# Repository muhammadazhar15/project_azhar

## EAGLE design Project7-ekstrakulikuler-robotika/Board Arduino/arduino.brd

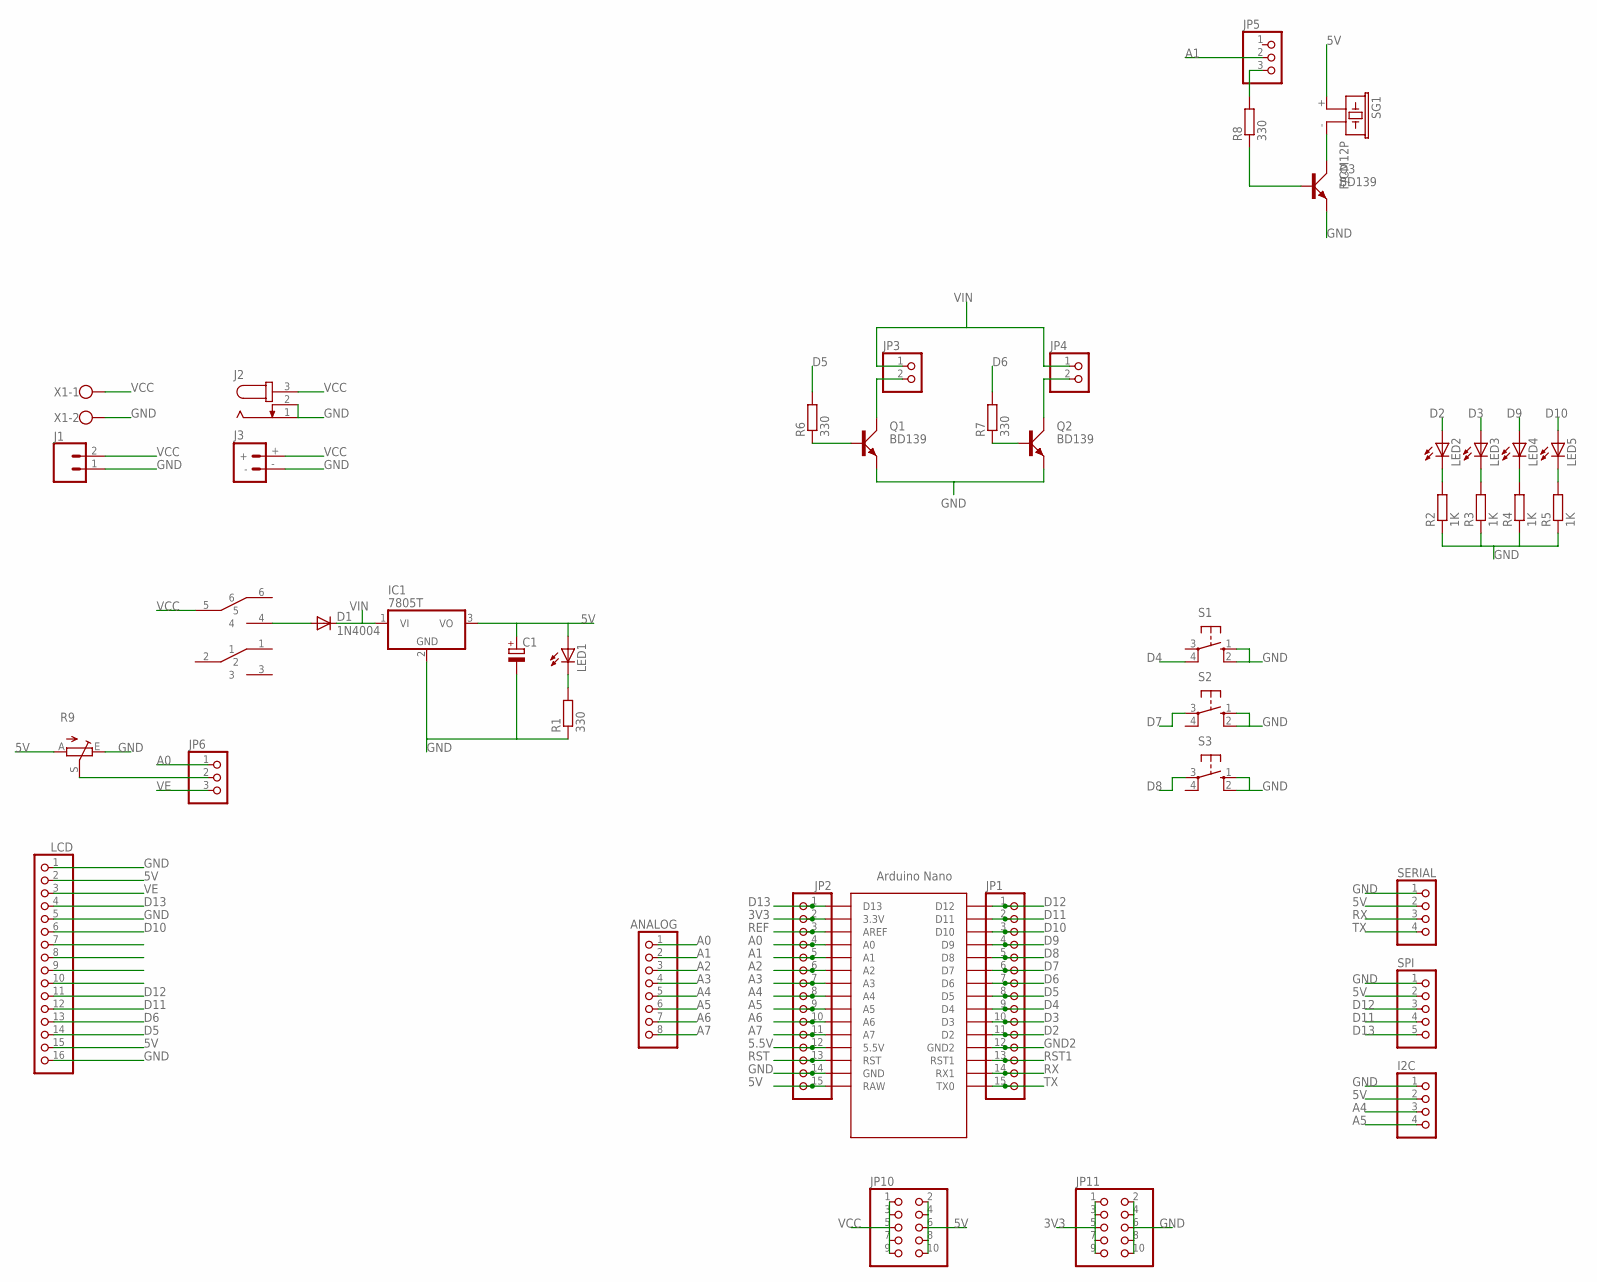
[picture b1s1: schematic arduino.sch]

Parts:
ANALOG: PINHD-1X8; 1X08
C1: CPOL-EUE5-8.5; E5-8,5
D1: 1N4004; DO41-10
I2C: PINHD-1X4; 1X04
IC1: 7805T; TO220H
J1: CONN_02POLAR_LOCK; MOLEX-1X2_LOCK
J2: JACK-PLUG0; SPC4077
J3: BATTERY_CONN_DEANS; DEANS
JP1, JP2: PINHD-1X15; 1X15
JP3, JP4: PINHD-1X2; 1X02
JP5, JP6: PINHD-1X3; 1X03
JP10, JP11: PINHD-2X5; 2X05
LCD: PINHD-1X16; 1X16
LED1, LED2, LED3, LED4, LED5: LED3MM
Q1, Q2, Q3: BD139; TO126AV
R1, R6, R7, R8: 330; 0207/7
R2, R3, R4, R5: 1K; 0207/7
R9: TRIM_EU-CA6V; CA6V
S1, S2, S3: 10-XX; B3F-10XX
SERIAL: PINHD-1X4; 1X04
SG1: F/CM12P
SPI: PINHD-1X5; 1X05
U$1: NANO
U$2: BUTTON-DPDT-7MM
X1: W237-102

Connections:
3V3: JP2.2, JP11.1, JP11.3, JP11.5, JP11.7, JP11.9, U$1.3.3V
5.5V: JP2.12, U$1.5V (5.5V)
5V: C1.+, I2C.2, IC1.3 (VO), JP2.15, JP10.2, JP10.4, JP10.6, JP10.8, JP10.10, LCD.2, LCD.15, LED1.A, R9.A, SERIAL.2, SG1.+ (1), SPI.2, U$1.RAW
A0: ANALOG.1, JP2.4, JP6.1, U$1.A0
A1: ANALOG.2, JP2.5, JP5.2, U$1.A1
A2: ANALOG.3, JP2.6, U$1.A2
A3: ANALOG.4, JP2.7, U$1.A3
A4: ANALOG.5, I2C.3, JP2.8, U$1.A4
A5: ANALOG.6, I2C.4, JP2.9, U$1.A5
A6: ANALOG.7, JP2.10, U$1.A6
A7: ANALOG.8, JP2.11, U$1.A7
D2: JP1.11, LED2.A, U$1.D2
D3: JP1.10, LED3.A, U$1.D3
D4: JP1.9, S1.4 (P1), U$1.D4
D5: JP1.8, LCD.14, R6.2, U$1.D5
D6: JP1.7, LCD.13, R7.2, U$1.D6
D7: JP1.6, S2.3, U$1.D7
D8: JP1.5, S3.3, U$1.D8
D9: JP1.4, LED4.A, U$1.D9
D10: JP1.3, LCD.6, LED5.A, U$1.D10
D11: JP1.2, LCD.12, SPI.4, U$1.D11
D12: JP1.1, LCD.11, SPI.3, U$1.D12
D13: JP2.1, LCD.4, SPI.5, U$1.D13
GND: C1.-, I2C.1, IC1.2 (GND), J1.1, J2.1, J2.2, J3.-, JP2.14, JP11.2, JP11.4, JP11.6, JP11.8, JP11.10, LCD.1, LCD.5, LCD.16, Q1.E, Q2.E, Q3.E, R1.1, R2.1, R3.1, R4.1, R5.1, R9.E, S1.1 (S), S1.2 (S1), S2.1 (S), S2.2 (S1), S3.1 (S), S3.2 (S1), SERIAL.1, SPI.1, U$1.GND, X1.2
GND2: JP1.12, U$1.GND1 (GND2)
unnamed: D1.A, U$2.4
unnamed: Q3.B, R8.1
unnamed: LED2.K (C), R2.2
unnamed: LED1.K (C), R1.2
unnamed: LED3.K (C), R3.2
unnamed: LED4.K (C), R4.2
unnamed: LED5.K (C), R5.2
unnamed: Q1.B, R6.1
unnamed: Q2.B, R7.1
unnamed: JP3.2, Q1.C
unnamed: JP4.2, Q2.C
unnamed: Q3.C, SG1.- (2)
unnamed: JP5.3, R8.2
unnamed: JP6.2, R9.S
REF: JP2.3, U$1.AREF
RST: JP2.13, U$1.RST
RST1: JP1.13, U$1.RST1
RX: JP1.14, SERIAL.3, U$1.RX1
TX: JP1.15, SERIAL.4, U$1.TX0
VCC: J1.2, J2.3, J3.+, JP10.1, JP10.3, JP10.5, JP10.7, JP10.9, U$2.5, X1.1
VE: JP6.3, LCD.3
VIN: D1.C, IC1.1 (VI), JP3.1, JP4.1

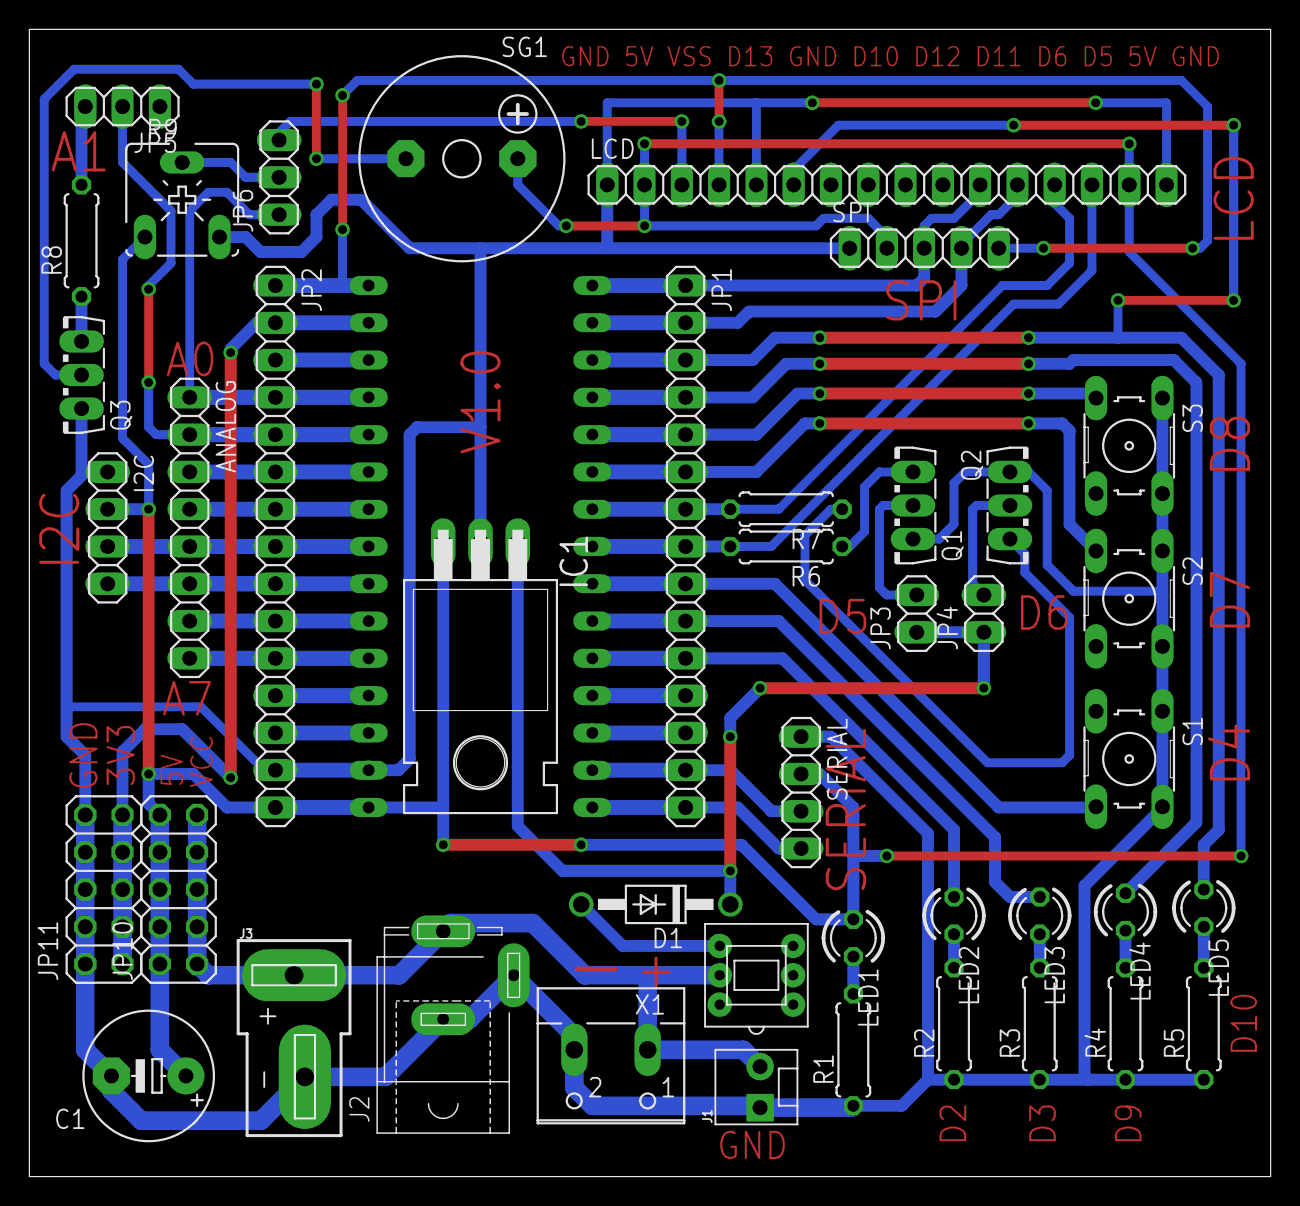
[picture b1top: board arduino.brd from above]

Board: 2 copper layers, 84.6 x 78.2 mm, 43 parts (0 on the bottom side), 47 nets.

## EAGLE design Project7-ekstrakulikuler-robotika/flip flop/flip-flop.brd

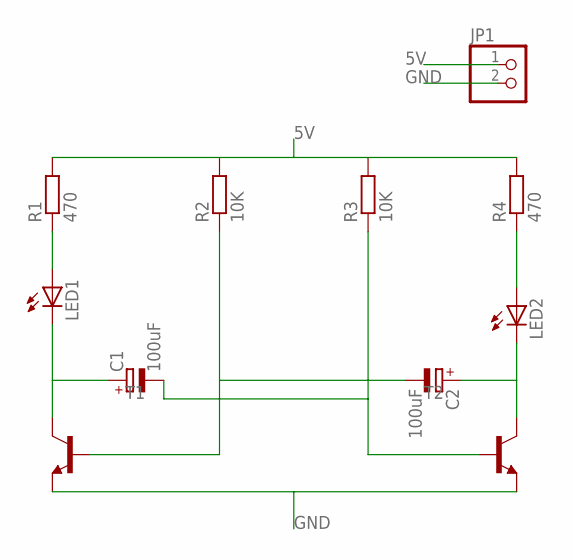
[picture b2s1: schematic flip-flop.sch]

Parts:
C1, C2: 100uF; E2,5-6
JP1: PINHD-1X2; 1X02
LED1, LED2: LED3MM
R1, R4: 470; 0207/7
R2, R3: 10K; 0207/7
T1, T2: BC547-NPN-TO92-CBE; TO92-CBE

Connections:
5V: JP1.1, R1.2, R2.2, R3.2, R4.2
GND: JP1.2, T1.E, T2.E
unnamed: LED1.A, R1.1
unnamed: LED2.A, R4.1
unnamed: C1.+, LED1.K (C), T1.C
unnamed: C2.+, LED2.K (C), T2.C
unnamed: C2.-, R2.1, T1.B
unnamed: C1.-, R3.1, T2.B

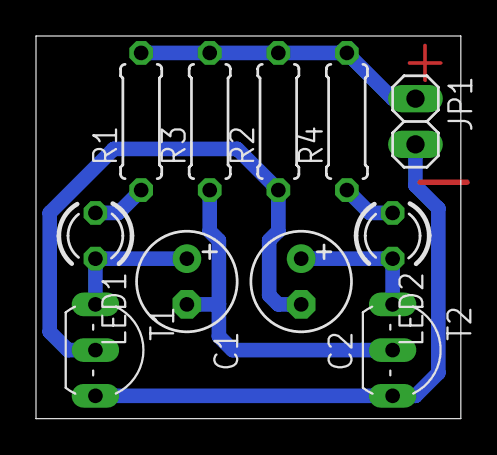
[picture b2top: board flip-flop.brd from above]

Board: 2 copper layers, 23.6 x 21.3 mm, 11 parts (0 on the bottom side), 8 nets.

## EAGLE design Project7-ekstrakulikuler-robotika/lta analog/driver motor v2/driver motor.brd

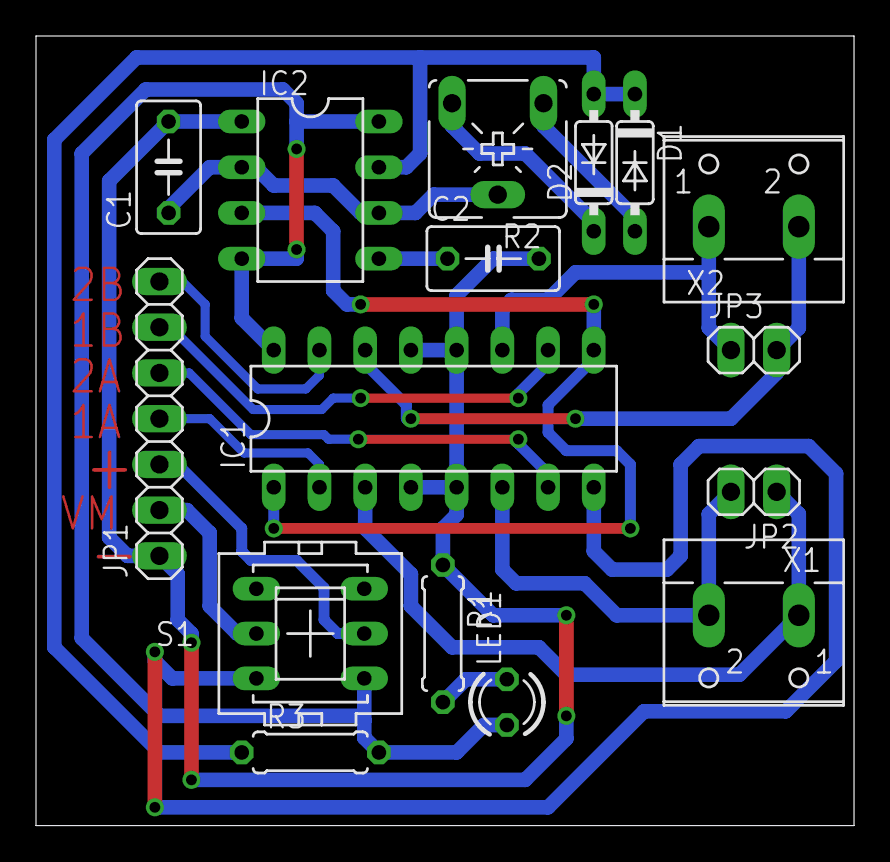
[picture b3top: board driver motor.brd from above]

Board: 2 copper layers, 45.4 x 43.9 mm, 16 parts (0 on the bottom side), 20 nets.

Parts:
C1, C2: C050-035X075
D1, D2: DO35-7
IC1: L293D; DIL16
IC2: NE555; DIL-08
JP1: 1X07
JP2, JP3: 1X02
LED1: LED3MM
R1: 330; 0207/7
R2: 10K; CA6V
R3: 1K; 0207/7
S1: PVA2R
X1, X2: W237-102

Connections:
1A: IC1.2, JP1.4
1B: IC1.10, JP1.6
2A: IC1.7, JP1.5
2B: IC1.15, JP1.7
5V: JP1.3, S1.2
GND: C1.2, C2.2, IC1.4, IC1.5, IC1.12, IC1.13, IC2.1, JP1.1, R1.1
unnamed: LED1.K, R1.2
unnamed: C2.1, IC2.5
unnamed: D1.C, D2.A, IC2.7, R3.1
unnamed: D1.A, R2.A
unnamed: D2.C, R2.E
unnamed: C1.1, IC2.2, IC2.6, R2.S
O1A: IC1.3, JP2.1, X1.1
O1B: IC1.11, JP3.1, X2.1
O2A: IC1.6, JP2.2, X1.2
O2B: IC1.14, JP3.2, X2.2
O5V: IC1.16, IC2.4, IC2.8, LED1.A, R3.2, S1.1
OVIN: IC1.8, S1.4
PWM: IC1.1, IC1.9, IC2.3
VIN: JP1.2, S1.5

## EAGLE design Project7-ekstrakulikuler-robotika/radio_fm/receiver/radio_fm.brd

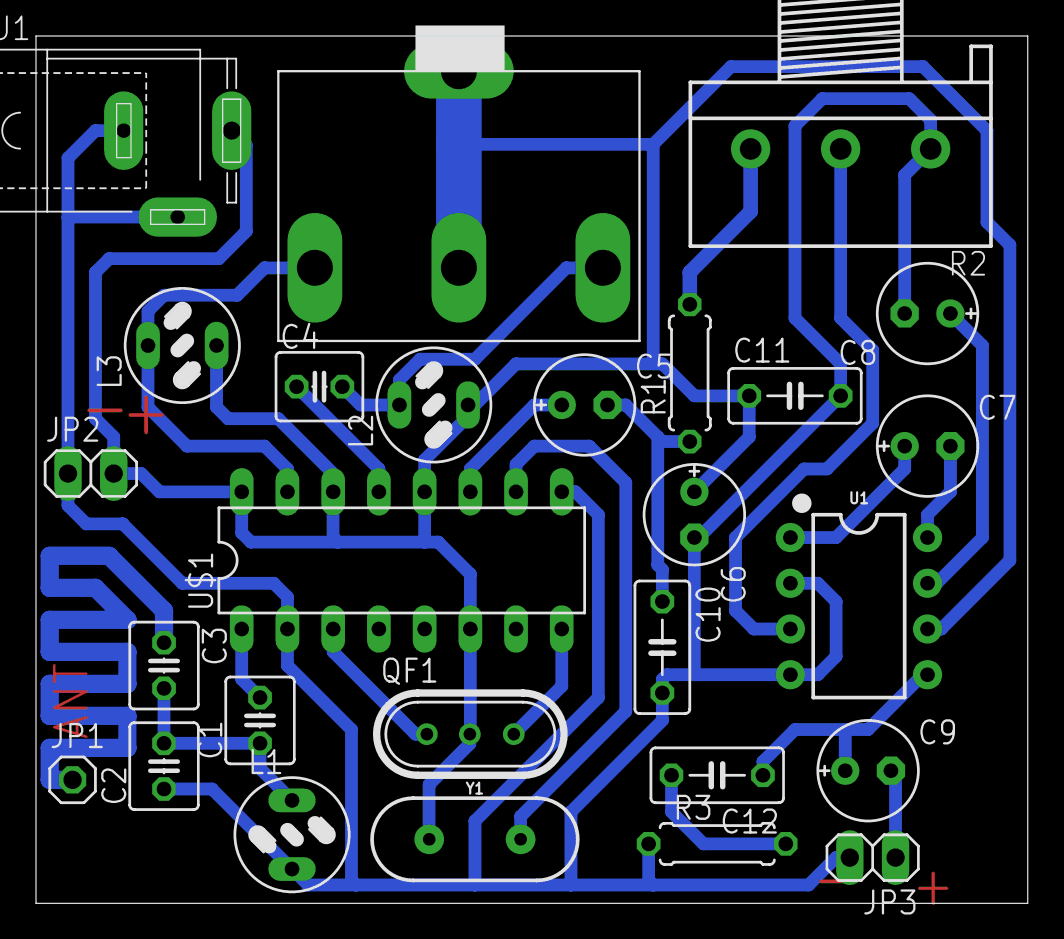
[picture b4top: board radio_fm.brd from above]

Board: 2 copper layers, 55.1 x 48.2 mm, 27 parts (0 on the bottom side), 21 nets.

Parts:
C1: 47PF; C025-040X050
C2, C3: 27PF; C025-040X050
C4: 15PF; C025-040X050
C5: 2.2uF; E2,5-6E
C6, C9: 100uF; E2,5-6E
C7: 4.7uF; E2,5-6E
C8: 10uF; E2,5-6E
C10: 10nF; C050-030X075
C11, C12: 100nF; C050-030X075
J1: SPC4077
JP1: 1X01
JP2, JP3: 1X02
L1, L2: 3; 82114R
L3: 4; 82114R
QF1: HC49U
R1: 10K; 0207/7
R2: 10K; 3RP/1610N
R3: 4.7; 0207/7
U1: LM386N; DIP08
U$1: TA2003; DIL16
U$2: VARCO_KEMATIAN_V2; VARCO_KEMATIAN2
Y1: HC49US

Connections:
GND: C2.1, C6.-, C8.-, C10.2, C11.2, J1.1, J1.2, JP2.1, JP3.2, L1.2, R2.1, R3.1, U1.2, U1.4, U$1.2, U$1.9
unnamed: C1.1, C2.2, C3.2, L1.1
unnamed: C3.1, JP1.1
unnamed: C1.2, U$1.1
unnamed: QF1.1, U$1.3
unnamed: QF1.3, U$1.8
unnamed: U$1.10, Y1.2
unnamed: C4.1, U$1.13
unnamed: L3.1, U$1.15, U$2.P$1
unnamed: C4.2, L2.1, U$2.P$3
unnamed: C5.-, C10.1, R1.1
unnamed: R1.2, R2.3
unnamed: R2.2, U1.3
unnamed: C12.2, R3.2
unnamed: C8.+, U1.7
unnamed: C9.+, C12.1, U1.5
unnamed: C7.-, U1.8
unnamed: C7.+, U1.1
unnamed: C9.-, JP3.1
SIGNAL: C5.+, U$1.11
VCC: C6.+, C11.1, J1.3, JP2.2, L2.2, L3.2, QF1.2, U1.6, U$1.6, U$1.12, U$1.14, U$1.16, U$2.P$2, U$2.P$4, Y1.1

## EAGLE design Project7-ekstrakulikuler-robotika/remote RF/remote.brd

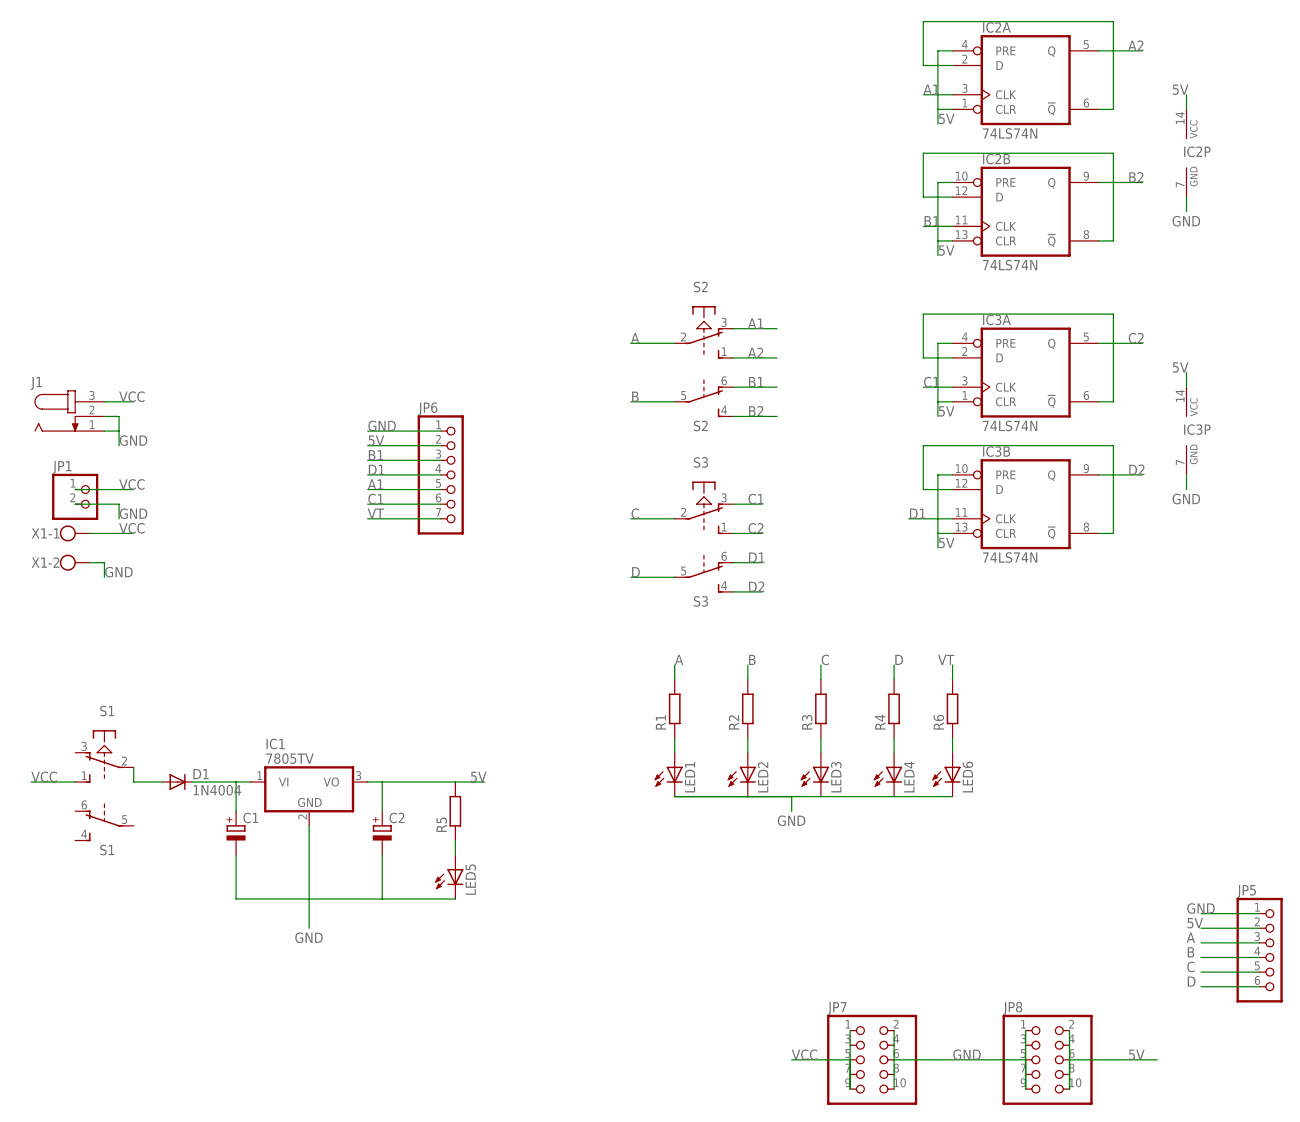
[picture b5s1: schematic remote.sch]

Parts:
C1, C2: CPOL-EUE2.5-5; E2,5-5
D1: 1N4004; DO41-10
IC1: 7805TV; TO220V
IC2, IC3: 74LS74N; DIL14
J1: JACK-PLUG0; SPC4077
JP1: PINHD-1X2; 1X02
JP5: PINHD-1X6; 1X06
JP6: PINHD-1X7; 1X07
JP7, JP8: PINHD-2X5; 2X05
LED1, LED2, LED3, LED4, LED5, LED6: LED3MM
R1, R2, R3, R4, R5, R6: R-EU_0207/7; 0207/7
S1, S2, S3: PVA2R
X1: W237-102

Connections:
5V: C2.+, IC1.3 (VO), IC2.1 (CLR), IC2.4 (PRE), IC2.10 (PRE), IC2.13 (CLR), IC2.14 (VCC), IC3.1 (CLR), IC3.4 (PRE), IC3.10 (PRE), IC3.13 (CLR), IC3.14 (VCC), JP5.2, JP6.2, JP8.2, JP8.4, JP8.6, JP8.8, JP8.10, R5.2
A: JP5.3, R1.2, S2.2
A1: IC2.3 (CLK), JP6.5, S2.3 (O)
A2: IC2.5 (Q), S2.1 (S)
B: JP5.4, R2.2, S2.5
B1: IC2.11 (CLK), JP6.3, S2.6 (O)
B2: IC2.9 (Q), S2.4 (S)
C: JP5.5, R3.2, S3.2
C1: IC3.3 (CLK), JP6.6, S3.3 (O)
C2: IC3.5 (Q), S3.1 (S)
D: JP5.6, R4.2, S3.5
D1: IC3.11 (CLK), JP6.4, S3.6 (O)
D2: IC3.9 (Q), S3.4 (S)
GND: C1.-, C2.-, IC1.2 (GND), IC2.7 (GND), IC3.7 (GND), J1.1, J1.2, JP1.2, JP5.1, JP6.1, JP7.2, JP7.4, JP7.6, JP7.8, JP7.10, JP8.1, JP8.3, JP8.5, JP8.7, JP8.9, LED1.K (C), LED2.K (C), LED3.K (C), LED4.K (C), LED5.K (C), LED6.K (C), X1.2
unnamed: D1.A, S1.2
unnamed: C1.+, D1.C, IC1.1 (VI)
unnamed: LED1.A, R1.1
unnamed: LED5.A, R5.1
unnamed: LED2.A, R2.1
unnamed: LED3.A, R3.1
unnamed: LED4.A, R4.1
unnamed: IC3.8 (!Q), IC3.12 (D)
unnamed: LED6.A, R6.1
unnamed: IC3.2 (D), IC3.6 (!Q)
unnamed: IC2.8 (!Q), IC2.12 (D)
unnamed: IC2.2 (D), IC2.6 (!Q)
VCC: J1.3, JP1.1, JP7.1, JP7.3, JP7.5, JP7.7, JP7.9, S1.1 (S), X1.1
VT: JP6.7, R6.2

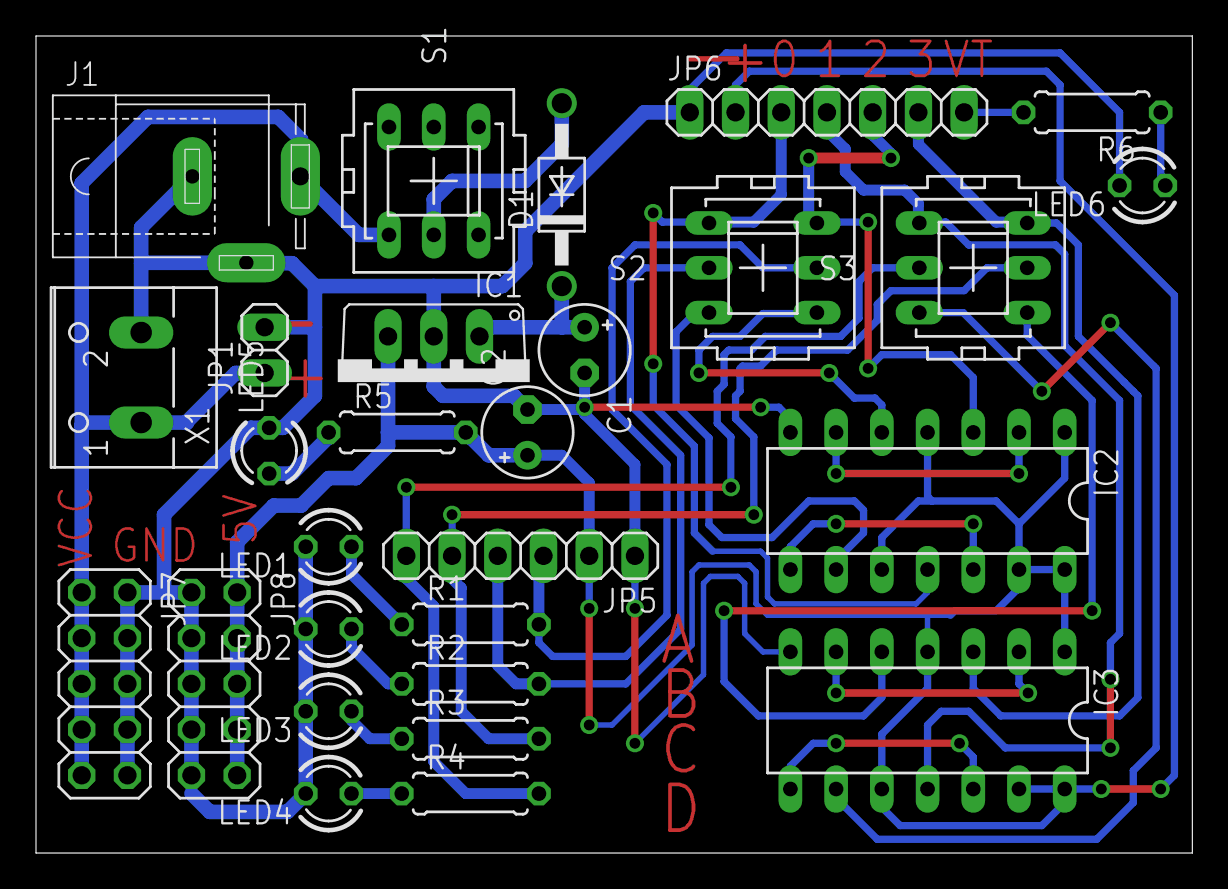
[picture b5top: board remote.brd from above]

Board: 2 copper layers, 64.2 x 45.4 mm, 28 parts (0 on the bottom side), 28 nets.

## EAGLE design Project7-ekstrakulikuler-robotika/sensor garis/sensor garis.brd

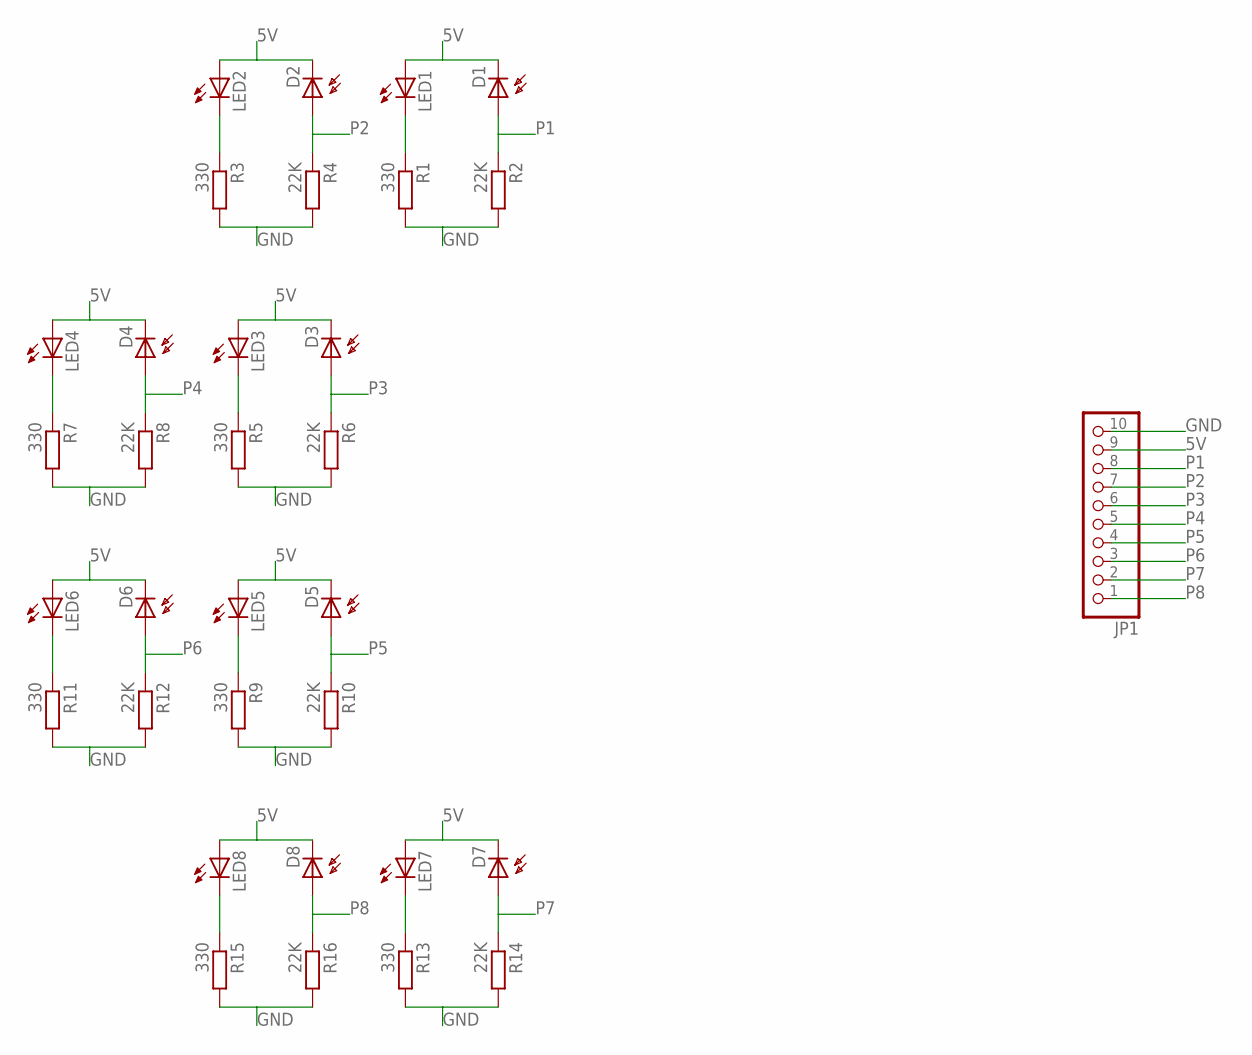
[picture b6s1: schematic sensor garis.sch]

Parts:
D1, D2, D3, D4, D5, D6, D7, D8: BPX65
JP1: PINHD-1X10; 1X10
LED1, LED2, LED3, LED4, LED5, LED6, LED7, LED8: LED3MM
R1, R3, R5, R7, R9, R11, R13, R15: 330; 0207/7
R2, R4, R6, R8, R10, R12, R14, R16: 22K; 0207/7

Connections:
5V: D1.K (C), D2.K (C), D3.K (C), D4.K (C), D5.K (C), D6.K (C), D7.K (C), D8.K (C), JP1.9, LED1.A, LED2.A, LED3.A, LED4.A, LED5.A, LED6.A, LED7.A, LED8.A
GND: JP1.10, R1.2, R2.2, R3.2, R4.2, R5.2, R6.2, R7.2, R8.2, R9.2, R10.2, R11.2, R12.2, R13.2, R14.2, R15.2, R16.2
unnamed: LED2.K (C), R3.1
unnamed: LED1.K (C), R1.1
unnamed: LED3.K (C), R5.1
unnamed: LED4.K (C), R7.1
unnamed: LED5.K (C), R9.1
unnamed: LED6.K (C), R11.1
unnamed: LED7.K (C), R13.1
unnamed: LED8.K (C), R15.1
P1: D1.A, JP1.8, R2.1
P2: D2.A, JP1.7, R4.1
P3: D3.A, JP1.6, R6.1
P4: D4.A, JP1.5, R8.1
P5: D5.A, JP1.4, R10.1
P6: D6.A, JP1.3, R12.1
P7: D7.A, JP1.2, R14.1
P8: D8.A, JP1.1, R16.1

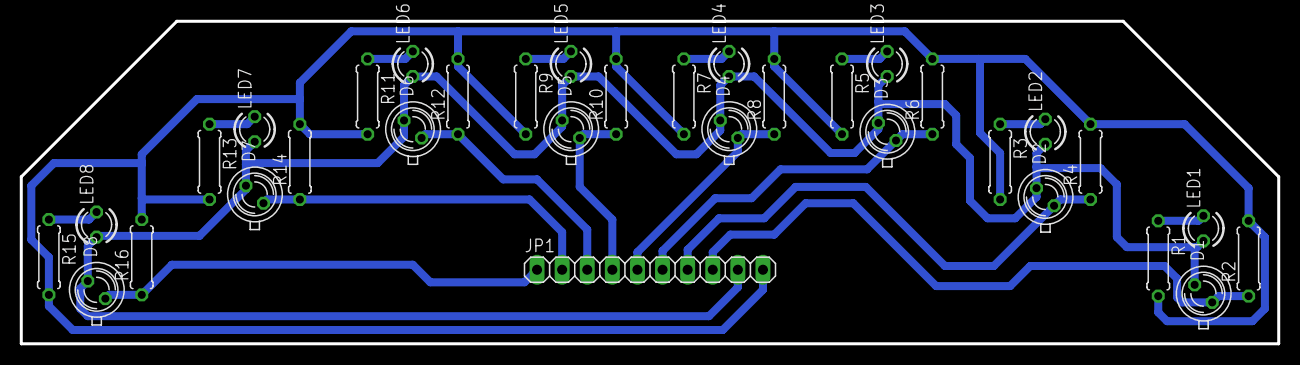
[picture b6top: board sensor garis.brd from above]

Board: 2 copper layers, 127.3 x 32.6 mm, 33 parts (0 on the bottom side), 18 nets.

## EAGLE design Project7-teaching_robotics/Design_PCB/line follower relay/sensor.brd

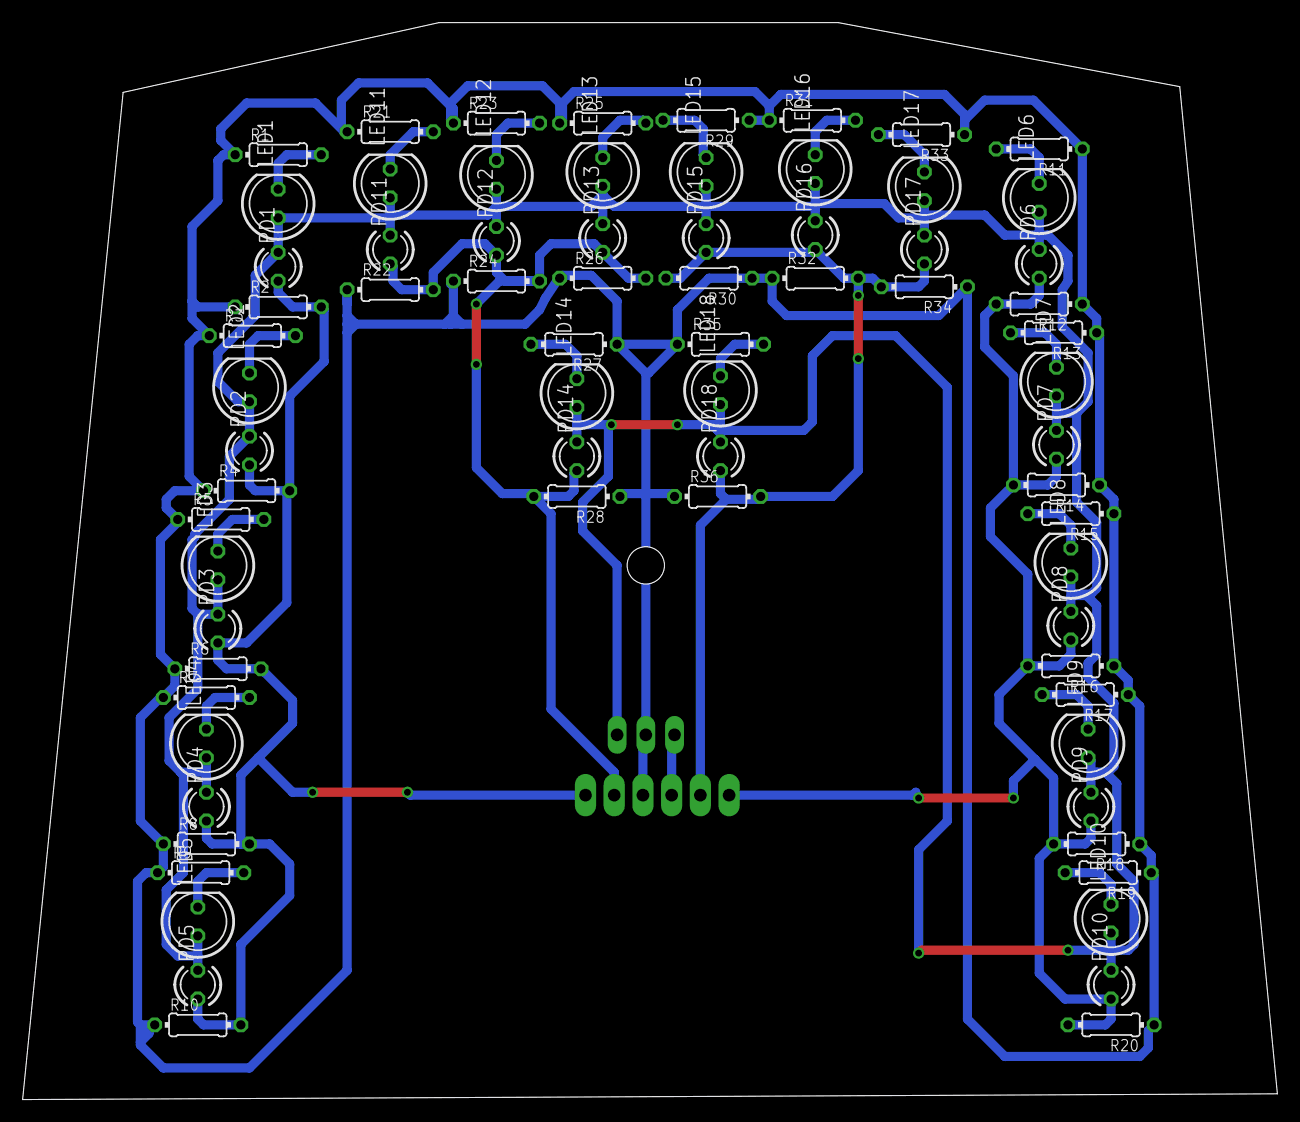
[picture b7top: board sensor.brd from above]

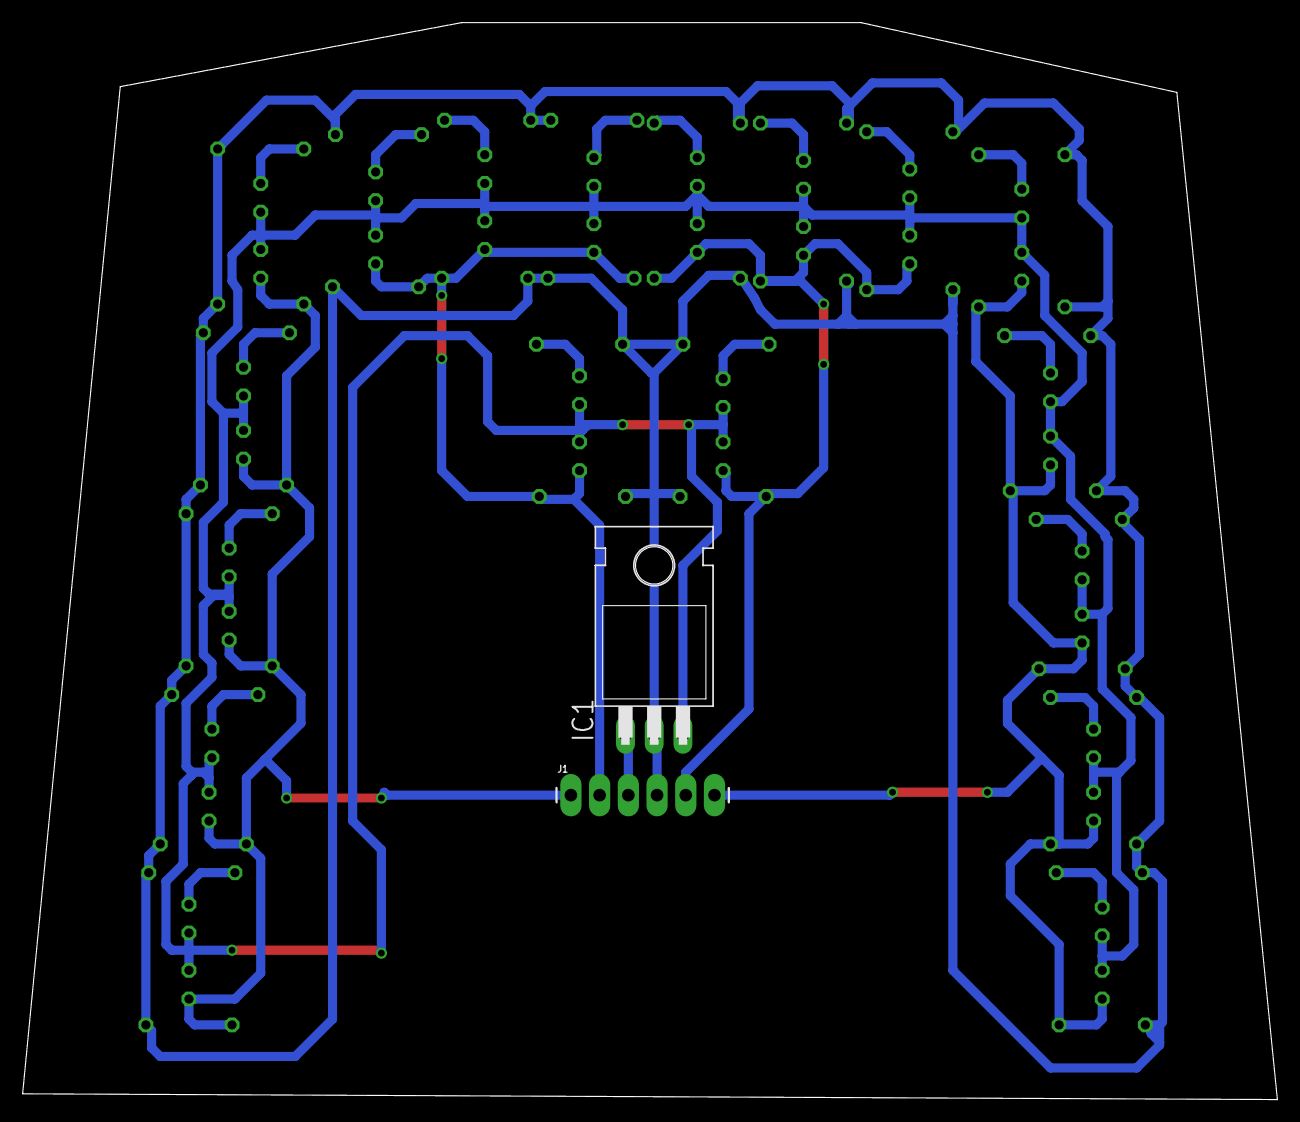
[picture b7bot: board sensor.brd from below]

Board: 2 copper layers, 111.0 x 95.2 mm, 74 parts (2 on the bottom side), 25 nets.

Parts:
IC1: 7805T; TO220H
J1: 1X06_LONGPADS
LED1, LED2, LED3, LED4, LED5, LED6, LED7, LED8, LED9, LED10, LED11, LED12, LED13, LED14, LED15, LED16, LED17, LED18: LED5MM
PD1, PD2, PD3, PD4, PD5, PD6, PD7, PD8, PD9, PD10, PD11, PD12, PD13, PD14, PD15, PD16, PD17, PD18: LED3MM
R1, R2, R3, R4, R5, R6, R7, R8, R9, R10, R11, R12, R13, R14, R15, R16, R17, R18, R19, R20, R21, R22, R23, R24, R25, R26, R27, R28, R29, R30, R31, R32, R33, R34, R35, R36: 0204/7

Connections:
GND: IC1.2, J1.4, R1.1, R2.1, R3.1, R4.1, R5.1, R6.1, R7.1, R8.1, R9.1, R10.1, R11.1, R12.1, R13.1, R14.1, R15.1, R16.1, R17.1, R18.1, R19.1, R20.1, R21.1, R22.1, R23.1, R24.1, R25.1, R26.1, R27.1, R28.1, R29.1, R30.1, R31.1, R32.1, R33.1, R34.1, R35.1, R36.1
KA: J1.2, PD15.A, PD16.A, PD17.A, PD18.A, R30.2, R32.2, R34.2, R36.2
KI: J1.5, PD11.A, PD12.A, PD13.A, PD14.A, R22.2, R24.2, R26.2, R28.2
unnamed: LED1.K, R1.2
unnamed: LED6.K, R11.2
unnamed: LED2.K, R3.2
unnamed: LED7.K, R13.2
unnamed: LED3.K, R5.2
unnamed: LED8.K, R15.2
unnamed: LED4.K, R7.2
unnamed: LED9.K, R17.2
unnamed: LED5.K, R9.2
unnamed: LED10.K, R19.2
unnamed: LED11.K, R21.2
unnamed: LED12.K, R23.2
unnamed: LED13.K, R25.2
unnamed: LED14.K, R27.2
unnamed: LED15.K, R29.2
unnamed: LED16.K, R31.2
unnamed: LED17.K, R33.2
unnamed: LED18.K, R35.2
SKA: J1.1, PD6.A, PD7.A, PD8.A, PD9.A, PD10.A, R12.2, R14.2, R16.2, R18.2, R20.2
SKI: J1.6, PD1.A, PD2.A, PD3.A, PD4.A, PD5.A, R2.2, R4.2, R6.2, R8.2, R10.2
VCC: IC1.3, LED1.A, LED2.A, LED3.A, LED4.A, LED5.A, LED6.A, LED7.A, LED8.A, LED9.A, LED10.A, LED11.A, LED12.A, LED13.A, LED14.A, LED15.A, LED16.A, LED17.A, LED18.A, PD1.K, PD2.K, PD3.K, PD4.K, PD5.K, PD6.K, PD7.K, PD8.K, PD9.K, PD10.K, PD11.K, PD12.K, PD13.K, PD14.K, PD15.K, PD16.K, PD17.K, PD18.K
VIN: IC1.1, J1.3

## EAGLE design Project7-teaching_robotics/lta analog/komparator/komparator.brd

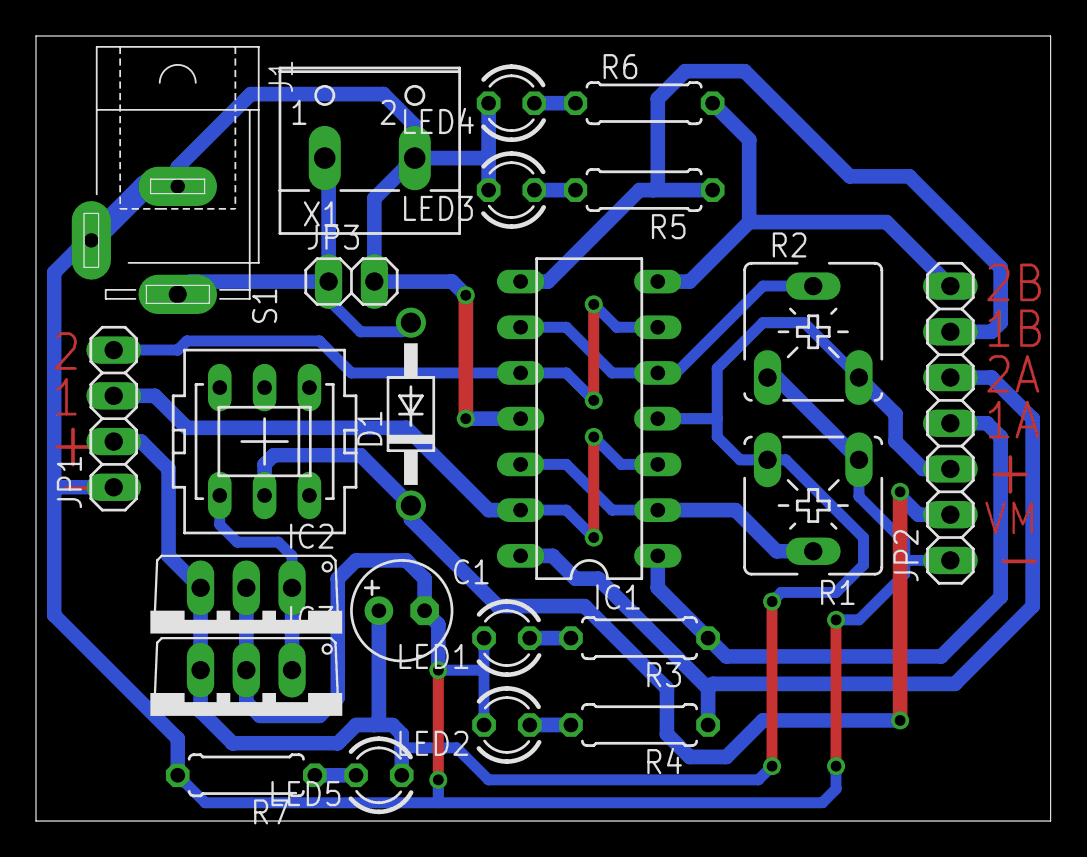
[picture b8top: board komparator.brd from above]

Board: 2 copper layers, 56.4 x 43.6 mm, 23 parts (0 on the bottom side), 18 nets.

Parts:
C1: 100uF; E2,5-6
D1: 1N4004; DO41-10
IC1: LM324N; DIL14
IC2, IC3: 7805TV; TO220V
J1: SPC4077
JP1: 1X04
JP2: 1X07
JP3: 1X02
LED1, LED2, LED3, LED4, LED5: LED3MM
R1, R2: CA6V
R3, R4, R5, R6: 1K; 0207/7
R7: 330; 0207/7
S1: PVA2R
X1: W237-102

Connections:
1A: IC1.1, JP2.4, R3.1
1B: IC1.8, JP2.6, R5.1
2A: IC1.14, JP2.5, R4.1
2B: IC1.7, JP2.7, R6.2
5V: C1.+, IC1.4, IC2.3, IC3.3, JP1.2, JP2.3, LED5.A, R1.E, R2.E
GND: C1.-, IC1.11, IC2.2, IC3.2, J1.1, J1.2, JP1.1, JP2.1, JP3.2, LED1.K, LED2.K, LED3.K, LED4.K, R1.A, R2.A, R7.2, X1.2
unnamed: IC1.2, IC1.12, R1.S
unnamed: IC1.5, IC1.9, R2.S
unnamed: IC2.1, IC3.1, S1.1
unnamed: LED1.A, R3.2
unnamed: LED2.A, R4.2
unnamed: LED3.A, R5.2
unnamed: LED4.A, R6.1
unnamed: LED5.K, R7.1
P1: IC1.3, IC1.13, JP1.3
P2: IC1.6, IC1.10, JP1.4
VCC: D1.A, J1.3, JP3.1, X1.1
VIN: D1.C, JP2.2, S1.2

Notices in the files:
parts and their libraries:
SparkFun-Connectors: Licensing: Creative Commons ShareAlike 4.0 International - https://creativecommons.org/licenses/by-sa/4.0
